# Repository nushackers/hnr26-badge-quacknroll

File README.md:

# hack&Roll 2026 "Quack & Roll" hardware badge

This repository contains both the hardware and firmware source files for the
Hack&Roll 2026 hardware badge.

## License

See the root directory's [LICENSE.md](./LICENSE.md) for more information on how
these materials are licensed.

## Acknowledgements

This Hack&Roll 2026 hardware badge would not have been possible without the
following people:

- **Terence** Chan Zun Mun ([@Hackin7](https://github.com/Hackin7)), for his
  invaluable knowledge and guidance in PCB design and hardware badge
  development, as well as liaising with Espressif Systems
- Lim **Yik Jin** ([@yikjin](https://github.com/yikjin)), for developing the
  hardware badge
- Park **Youngseo** ([@youngseopark05](https://github.com/youngseopark05)), for
  creating the artwork used for this hardware badge
- Koh Chan Hong, **Ravern** ([@ravern](https://github.com/ravern)), for liaising
  with Espressif Systems
- Tan Rongwen, **Daren** ([@darentanrw](https://github.com/darentanrw)), for
  liaising with Espressif Systems
- Everyone in [NUS Hackers](https://www.nushackers.org/) for making Hack&Roll
  2026 a reality!

The ESP32-C3-WROOM-02-N4 module in this hardware badge is also sponsored by
[Espressif Systems](https://www.espressif.com/), the manufacturers of the
widely-used ESP32 chips.

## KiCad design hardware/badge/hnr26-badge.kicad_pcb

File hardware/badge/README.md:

# HnR'26 hardware badge: hardware source files

This directory contains the [KiCad](https://www.kicad.org/) 9 hardware source
files for the Hack&Roll 2026 hardware badge.

## Manufacturing

We used [JLCPCB manufacturing services](https://jlcpcb.com/) for the hardware
badges. To help with component parts assignment and generating JLCPCB-compatible
files, we used the open source
[KiCAD JLCPCB tools](https://github.com/bouni/kicad-jlcpcb-tools) plugin.

## License

The hardware source files in this directory are open-sourced, licensed under
CERN-OHL-P-2.0. See [LICENSE.md](./LICENSE.md) for the full license text.

## Acknowledgements

HnR'26 hardware badge would not have been possible without the following people:

- **Terence** Chan Zun Mun ([@Hackin7](https://github.com/Hackin7)), for his
  invaluable knowledge and guidance in PCB design and hardware badge
  development, as well as liaising with Espressif Systems
- Lim **Yik Jin** ([@yikjin](https://github.com/yikjin)), for developing the
  hardware badge
- Park **Youngseo** ([@youngseopark05](https://github.com/youngseopark05)), for
  creating the artwork used for this hardware badge, and for HnR'26 in general
- **Daren** Tan Rongwen ([@darentanrw](https://github.com/darentanrw)), for
  liaising with Espressif Systems

The ESP32-C3-WROOM-02-N4 module in this hardware badge is also sponsored by
[Espressif Systems](https://www.espressif.com/), the manufacturers of the
widely-used ESP32 chips.

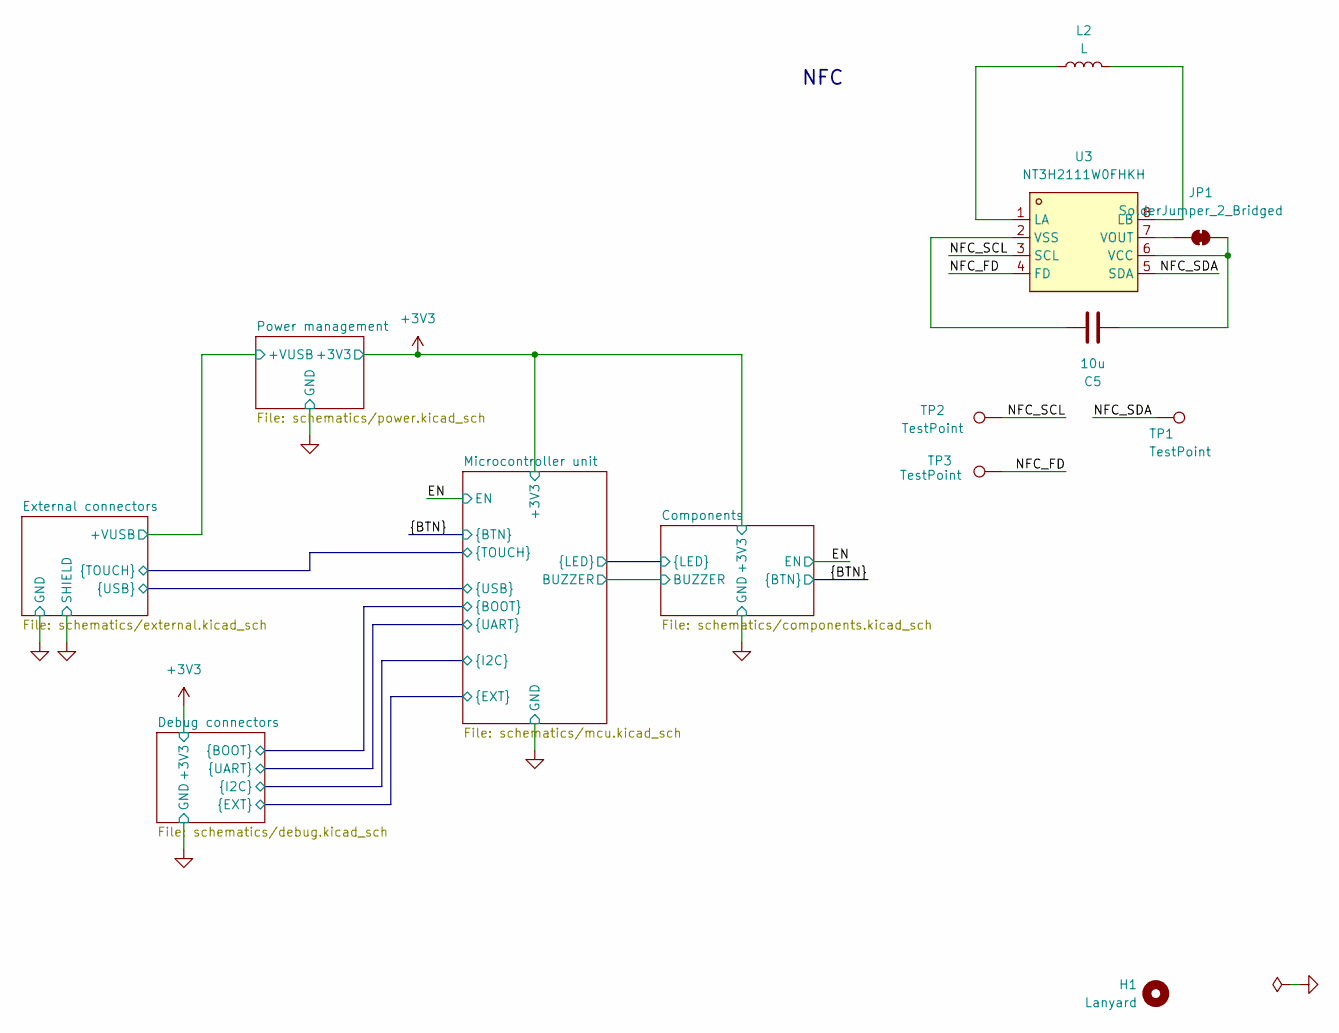
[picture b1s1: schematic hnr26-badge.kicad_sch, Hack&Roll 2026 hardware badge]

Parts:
C5: 10u; C_0805_2012Metric; LCSC Part # C19103847
H1: Lanyard; MountingHole_3.2mm_M3_DIN965_Pad
JP1: SolderJumper_2_Bridged; SolderJumper-2_P1.3mm_Bridged_RoundedPad1.0x1.5mm
L2: L; NFC_COIL
TP1, TP2, TP3: TestPoint; TestPoint_Pad_1.0x1.0mm
U3: NT3H2111W0FHKH; XQFN-8_L1.6-W1.6-P0.50-BL_NT3H2111W0FHKH; LCSC Part C710403

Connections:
/NFC_FD: TP3.1, U3.4 (FD)
/NFC_SCL: TP2.1, U3.3 (SCL)
/NFC_SDA: TP1.1, U3.5 (SDA)
unnamed: C5.2, JP1.1 (A), U3.6 (VCC)
unnamed: JP1.2 (B), U3.7 (VOUT)
unnamed: L2.1, U3.1 (LA)
unnamed: L2.2, U3.8 (LB)
unnamed: C5.1, U3.2 (VSS)

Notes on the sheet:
NFC

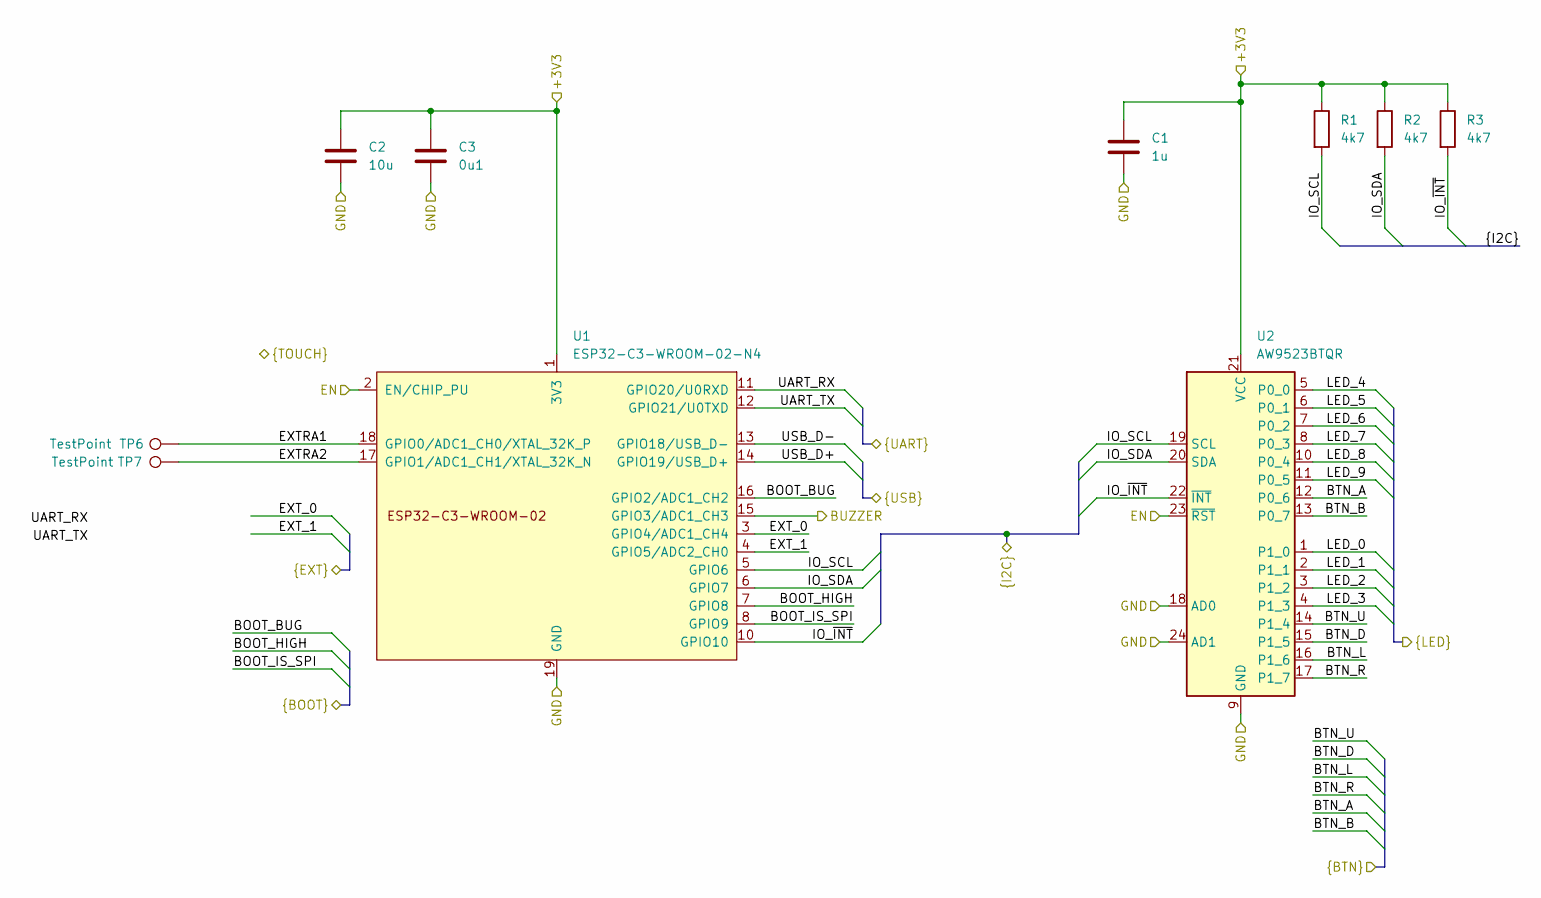
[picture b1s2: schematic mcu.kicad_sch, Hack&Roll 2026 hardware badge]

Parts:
C1: 1u; C_0805_2012Metric; LCSC Part # C344171
C2: 10u; C_0805_2012Metric; LCSC Part # C19103847
C3: 0u1; C_0805_2012Metric; LCSC Part # C5137467
R1, R2, R3: 4k7; R_0805_2012Metric; LCSC Part # C2907326
TP6, TP7: TestPoint; TestPoint_Pad_2.5x2.5mm
U1: ESP32-C3-WROOM-02-N4; ESP32-C3-WROOM-02; LCSC Part # C2934560
U2: AW9523BTQR; QFN-24-1EP_4x4mm_P0.5mm_EP2.7x2.7mm; LCSC Part # C148077

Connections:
+3V3: C1.1, C2.1, C3.1, R1.1, R2.1, R3.1, U1.1 (3V3), U2.21 (VCC); also elsewhere on the board
/BTN_A: U2.12 (P0_6)
/BTN_B: U2.13 (P0_7)
/BTN_D: U2.15 (P1_5); also elsewhere on the board
/BTN_L: U2.16 (P1_6); also elsewhere on the board
/BTN_R: U2.17 (P1_7); also elsewhere on the board
/BTN_U: U2.14 (P1_4); also elsewhere on the board
/Components/BUZZER: U1.15 (GPIO3/ADC1_CH3); also elsewhere on the board
/Components/LED_0: U2.1 (P1_0); also elsewhere on the board
/Components/LED_1: U2.2 (P1_1); also elsewhere on the board
/Components/LED_2: U2.3 (P1_2); also elsewhere on the board
/Components/LED_3: U2.4 (P1_3); also elsewhere on the board
/Components/LED_4: U2.5 (P0_0); also elsewhere on the board
/Components/LED_5: U2.6 (P0_1); also elsewhere on the board
/Components/LED_6: U2.7 (P0_2); also elsewhere on the board
/Components/LED_7: U2.8 (P0_3); also elsewhere on the board
/Components/LED_8: U2.10 (P0_4); also elsewhere on the board
/Components/LED_9: U2.11 (P0_5); also elsewhere on the board
/Debug connectors/BOOT_BUG: U1.16 (GPIO2/ADC1_CH2); also elsewhere on the board
/Debug connectors/BOOT_HIGH: U1.7 (GPIO8); also elsewhere on the board
/Debug connectors/BOOT_IS_SPI: U1.8 (GPIO9); also elsewhere on the board
/Debug connectors/EXT_0: U1.3 (GPIO4/ADC1_CH4); also elsewhere on the board
/Debug connectors/EXT_1: U1.4 (GPIO5/ADC2_CH0); also elsewhere on the board
/Debug connectors/UART_RX: U1.11 (GPIO20/U0RXD); also elsewhere on the board
/Debug connectors/UART_TX: U1.12 (GPIO21/U0TXD); also elsewhere on the board
/EN: U1.2 (EN/CHIP_PU), U2.23 (~RST); also elsewhere on the board
/External connectors/USB_D+: U1.14 (GPIO19/USB_D+); also elsewhere on the board
/External connectors/USB_D-: U1.13 (GPIO18/USB_D-); also elsewhere on the board
/Microcontroller unit/EXTRA1: TP6.1, U1.18 (GPIO0/ADC1_CH0/XTAL_32K_P)
/Microcontroller unit/EXTRA2: TP7.1, U1.17 (GPIO1/ADC1_CH1/XTAL_32K_N)
/Microcontroller unit/IO_SCL: R1.2, U1.5 (GPIO6), U2.19 (SCL); also elsewhere on the board
/Microcontroller unit/IO_SDA: R2.2, U1.6 (GPIO7), U2.20 (SDA); also elsewhere on the board
/Microcontroller unit/IO_~INT: R3.2, U1.10 (GPIO10), U2.22 (~INT)
GND: C1.2, C2.2, C3.2, U1.9 (GND), U1.19 (GND), U2.9 (GND), U2.18 (AD0), U2.24 (AD1), U2.25 (GND); also elsewhere on the board

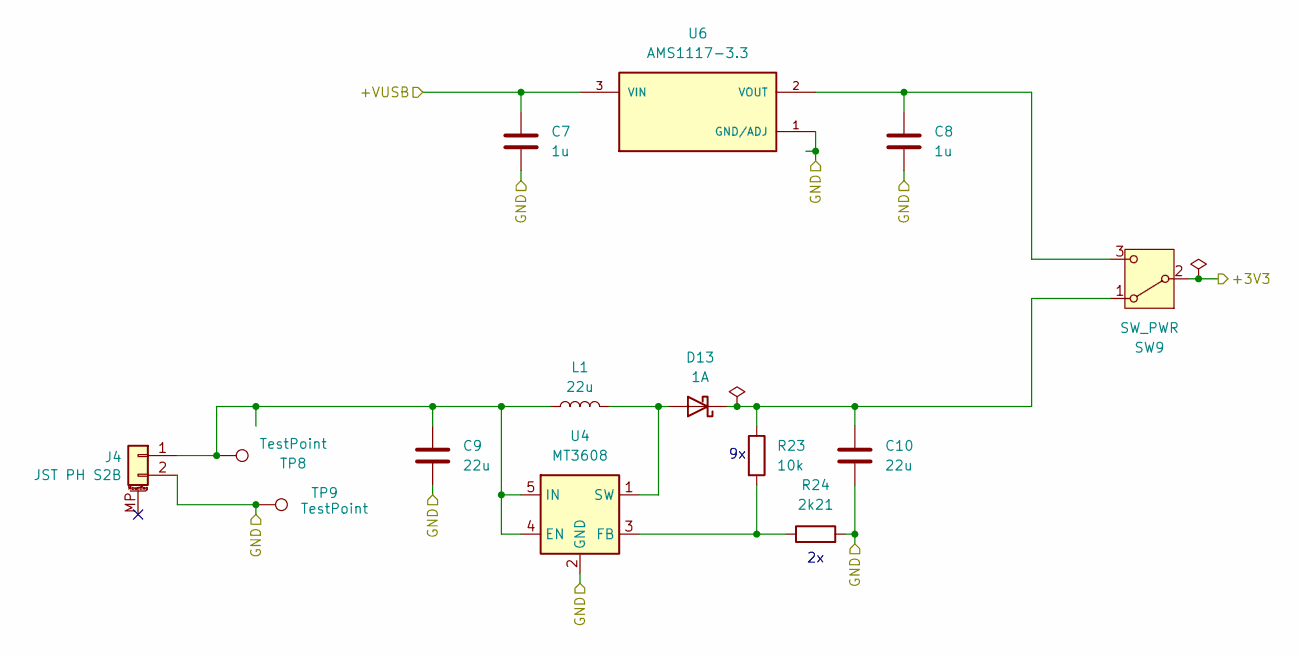
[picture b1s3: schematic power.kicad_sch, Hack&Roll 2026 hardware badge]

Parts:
C7, C8: 1u; C_0805_2012Metric; LCSC Part # C344171
C9, C10: 22u; C_0805_2012Metric; LCSC Part # C5674
D13: 1A; D_0805_2012Metric; LCSC Part # C143773
J4: JST PH S2B; JST_PH_S2B-PH-SM4-TB_1x02-1MP_P2.00mm_Horizontal; LCSC C505023
L1: 22u; L_0805_2012Metric; LCSC Part # C32375
R23: 10k; R_0805_2012Metric; LCSC Part # C2930231
R24: 2k21; R_0805_2012Metric; LCSC Part # C5121533
SW9: SW_PWR; SW-SMD_SK-01A-H1.5; LCSC Part # C778186
TP8, TP9: TestPoint; TestPoint_Pad_4.0x4.0mm
U4: MT3608; SOT-23-6; LCSC Part # C84817
U6: AMS1117-3.3; SOT-89-3_L4.5-W2.5-P1.50-LS4.2-BR; PARTREV N/A

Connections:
+3V3: SW9.2 (B); also elsewhere on the board
/External connectors/+VUSB: C7.1, U6.3 (VIN); also elsewhere on the board
GND: C7.2, C8.2, C9.2, C10.2, J4.2, R24.2, TP9.1, U4.2 (GND), U6.1 (GND/ADJ); also elsewhere on the board
unnamed: D13.2 (A), L1.2, U4.1 (SW)
unnamed: C10.1, D13.1 (K), R23.1, SW9.1 (A)
unnamed: C9.1, J4.1, L1.1, TP8.1, U4.4 (EN), U4.5 (IN)
unnamed: C8.1, SW9.3 (C), U6.2 (VOUT)
unnamed: R23.2, R24.1, U4.3 (FB)

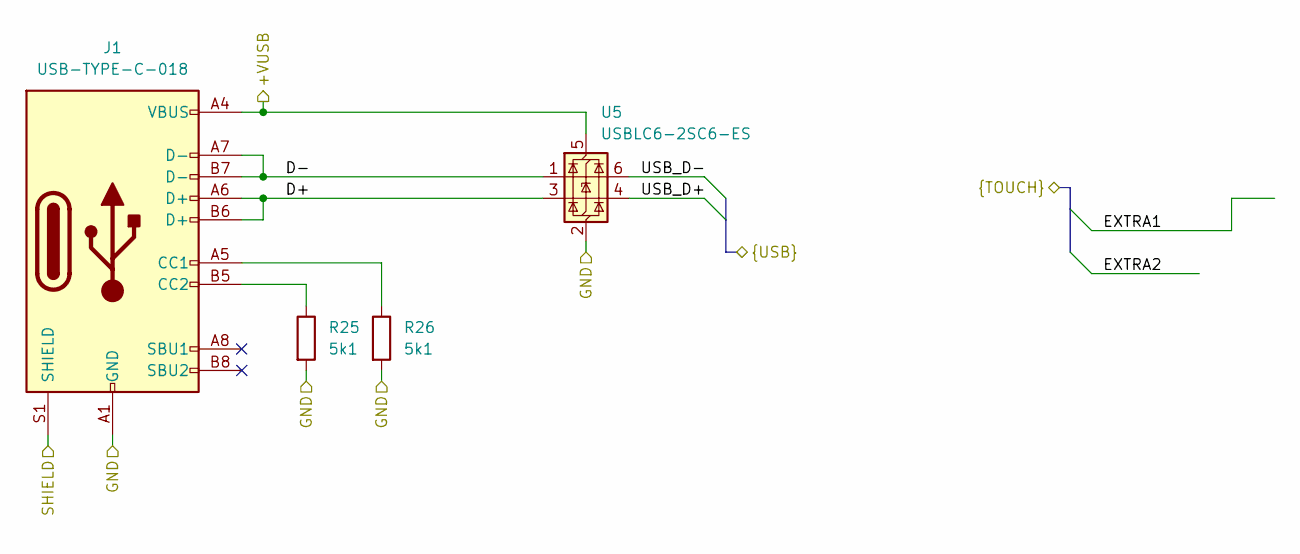
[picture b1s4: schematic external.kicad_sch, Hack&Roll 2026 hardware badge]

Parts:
J1: USB-TYPE-C-018; USB_C_Receptacle_GCT_USB4105-xx-A_16P_TopMnt_Horizontal; LCSC Part # C2927038
R25, R26: 5k1; R_0805_2012Metric; LCSC Part # C22356678
U5: USBLC6-2SC6-ES; SOT-23-6; LCSC Part # C5180249

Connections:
/External connectors/+VUSB: J1.A4 (VBUS), J1.A9 (VBUS), J1.B4 (VBUS), J1.B9 (VBUS), U5.5 (VBUS); also elsewhere on the board
/External connectors/D+: J1.A6 (D+), J1.B6 (D+), U5.3 (I/O2)
/External connectors/D-: J1.A7 (D-), J1.B7 (D-), U5.1 (I/O1)
/External connectors/USB_D+: U5.4 (I/O2); also elsewhere on the board
/External connectors/USB_D-: U5.6 (I/O1); also elsewhere on the board
GND: J1.A1 (GND), J1.A12 (GND), J1.B1 (GND), J1.B12 (GND), J1.S1 (SHIELD), R25.2, R26.2, U5.2 (GND); also elsewhere on the board
unnamed: J1.A5 (CC1), R26.1
unnamed: J1.B5 (CC2), R25.1

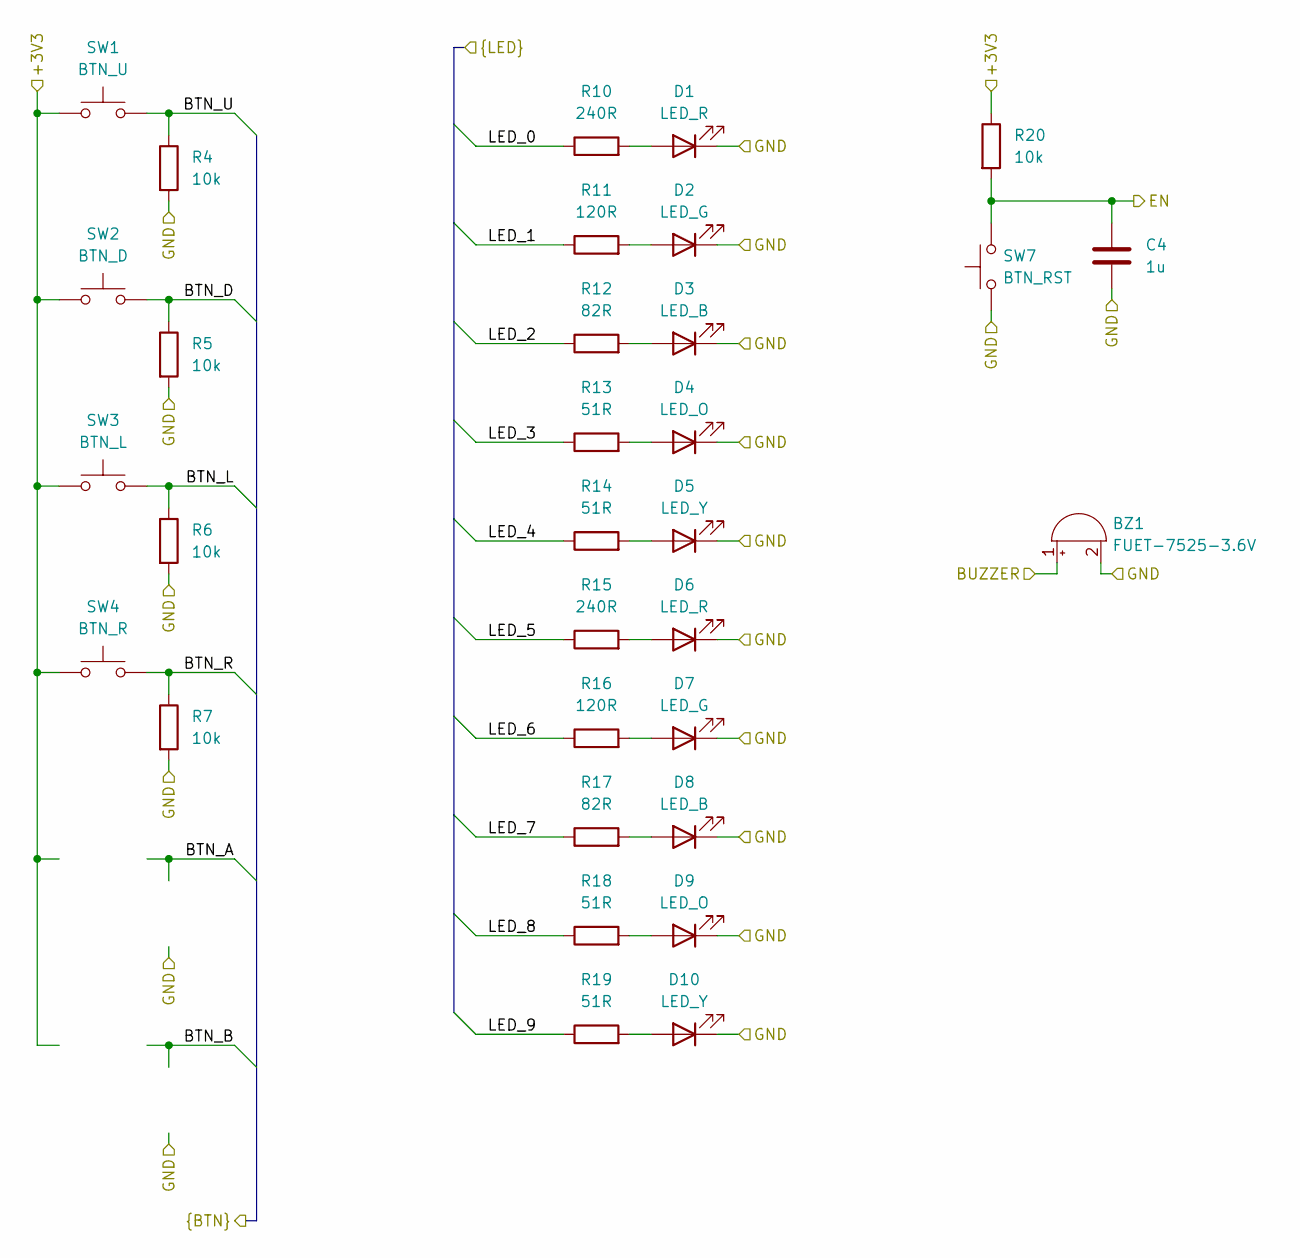
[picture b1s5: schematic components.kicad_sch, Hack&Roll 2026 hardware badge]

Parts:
BZ1: FUET-7525-3.6V; Buzzer-SMD_4P-L7.5-W7.5-BR; LCSC Part # C417427
C4: 1u; C_0805_2012Metric; LCSC Part # C344171
D1, D6: LED_R; LED_0805_2012Metric; LCSC Part # C7496834
D2, D7: LED_G; LED_0805_2012Metric; LCSC Part # C7496832
D3, D8: LED_B; LED_0805_2012Metric; LCSC Part # C7496833
D4, D9: LED_O; LED_0805_2012Metric; LCSC Part # C965813
D5, D10: LED_Y; LED_0805_2012Metric; LCSC Part # C965814
R4, R5, R6, R7, R20: 10k; R_0805_2012Metric; LCSC Part # C2930231
R10, R15: 240R; R_0805_2012Metric; LCSC Part # C25296
R11, R16: 120R; R_0805_2012Metric; LCSC Part # C3013232
R12, R17: 82R; R_0805_2012Metric; LCSC Part # C2907344
R13, R14, R18, R19: 51R; R_0805_2012Metric; LCSC Part # C2907334
SW1: BTN_U; SW_Push_1P1T_XKB_TS-1187A; LCSC Part # C2888877
SW2: BTN_D; SW_Push_1P1T_XKB_TS-1187A; LCSC Part # C2888877
SW3: BTN_L; SW_Push_1P1T_XKB_TS-1187A; LCSC Part # C2888877
SW4: BTN_R; SW_Push_1P1T_XKB_TS-1187A; LCSC Part # C2888877
SW7: BTN_RST; SW_Push_1P1T_XKB_TS-1187A; LCSC Part # C2888877

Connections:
+3V3: R20.1, SW1.1, SW2.1, SW3.1, SW4.1; also elsewhere on the board
/BTN_D: R5.1, SW2.2; also elsewhere on the board
/BTN_L: R6.1, SW3.2; also elsewhere on the board
/BTN_R: R7.1, SW4.2; also elsewhere on the board
/BTN_U: R4.1, SW1.2; also elsewhere on the board
/Components/BUZZER: BZ1.1 (+); also elsewhere on the board
/Components/LED_0: R10.1; also elsewhere on the board
/Components/LED_1: R11.1; also elsewhere on the board
/Components/LED_2: R12.1; also elsewhere on the board
/Components/LED_3: R13.1; also elsewhere on the board
/Components/LED_4: R14.1; also elsewhere on the board
/Components/LED_5: R15.1; also elsewhere on the board
/Components/LED_6: R16.1; also elsewhere on the board
/Components/LED_7: R17.1; also elsewhere on the board
/Components/LED_8: R18.1; also elsewhere on the board
/Components/LED_9: R19.1; also elsewhere on the board
/EN: C4.1, R20.2, SW7.2; also elsewhere on the board
GND: BZ1.2 (-), C4.2, D1.1 (K), D2.1 (K), D3.1 (K), D4.1 (K), D5.1 (K), D6.1 (K), D7.1 (K), D8.1 (K), D9.1 (K), D10.1 (K), R4.2, R5.2, R6.2, R7.2, SW7.1; also elsewhere on the board
unnamed: D1.2 (A), R10.2
unnamed: D2.2 (A), R11.2
unnamed: D3.2 (A), R12.2
unnamed: D4.2 (A), R13.2
unnamed: D5.2 (A), R14.2
unnamed: D6.2 (A), R15.2
unnamed: D7.2 (A), R16.2
unnamed: D8.2 (A), R17.2
unnamed: D9.2 (A), R18.2
unnamed: D10.2 (A), R19.2

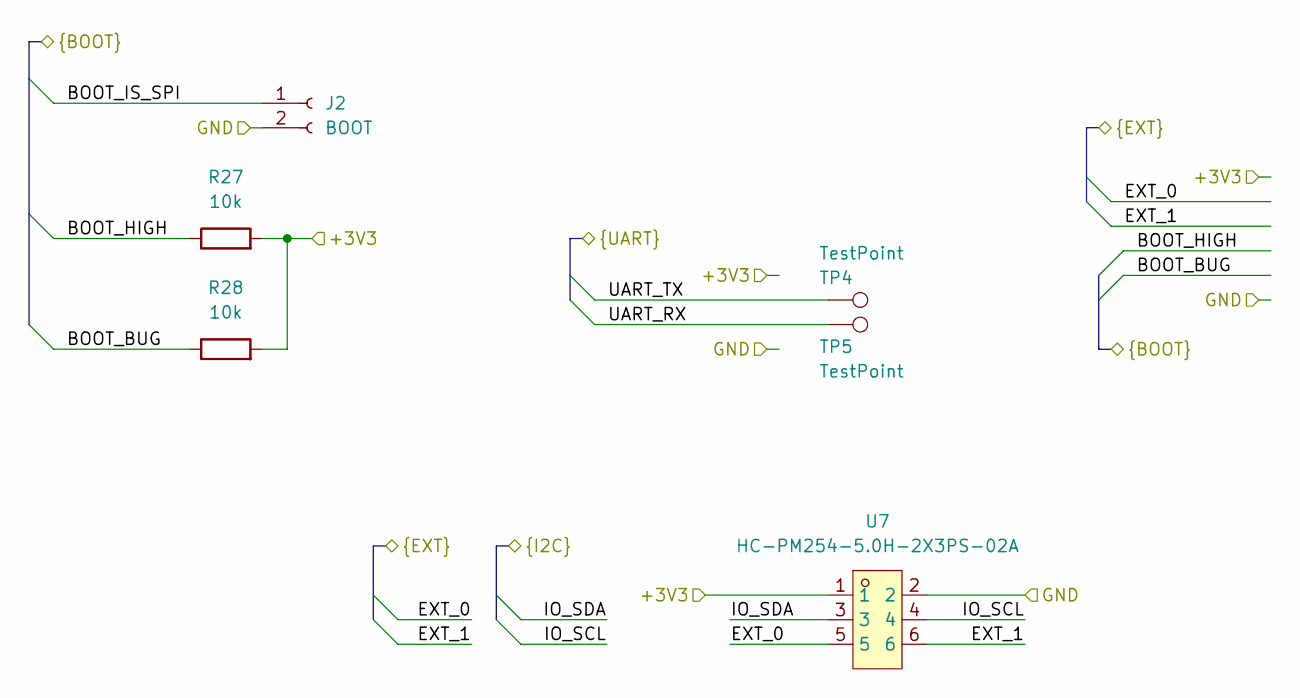
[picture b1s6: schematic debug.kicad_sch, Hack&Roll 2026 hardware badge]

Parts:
J2: BOOT; PinSocket_1x02_P2.54mm_Vertical
R27, R28: 10k; R_0805_2012Metric; LCSC Part # C2930231
TP4, TP5: TestPoint; TestPoint_Pad_2.5x2.5mm
U7: HC-PM254-5.0H-2X3PS-02A; CONN-SMD_HC-PM254-5.0H-2X3PS-02A; LCSC Part C42163131

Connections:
+3V3: R27.2, R28.2, U7.1; also elsewhere on the board
/Debug connectors/BOOT_BUG: R28.1; also elsewhere on the board
/Debug connectors/BOOT_HIGH: R27.1; also elsewhere on the board
/Debug connectors/BOOT_IS_SPI: J2.1; also elsewhere on the board
/Debug connectors/EXT_0: U7.5; also elsewhere on the board
/Debug connectors/EXT_1: U7.6; also elsewhere on the board
/Debug connectors/UART_RX: TP5.1; also elsewhere on the board
/Debug connectors/UART_TX: TP4.1; also elsewhere on the board
/Microcontroller unit/IO_SCL: U7.4; also elsewhere on the board
/Microcontroller unit/IO_SDA: U7.3; also elsewhere on the board
GND: J2.2, U7.2; also elsewhere on the board

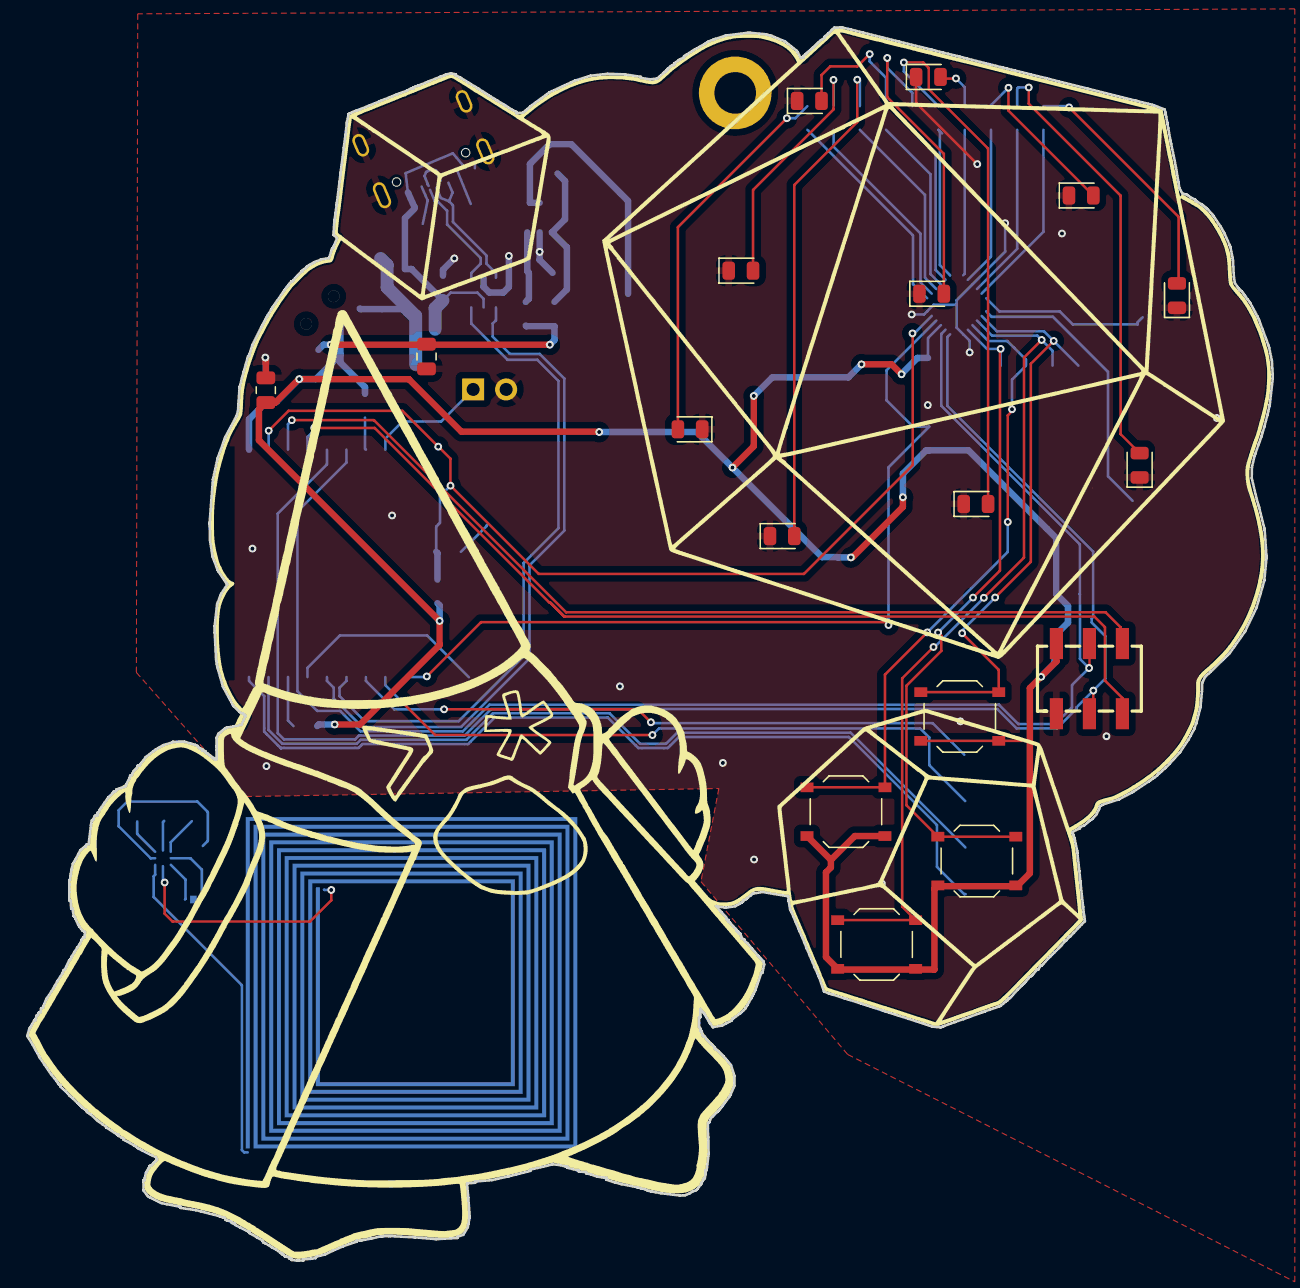
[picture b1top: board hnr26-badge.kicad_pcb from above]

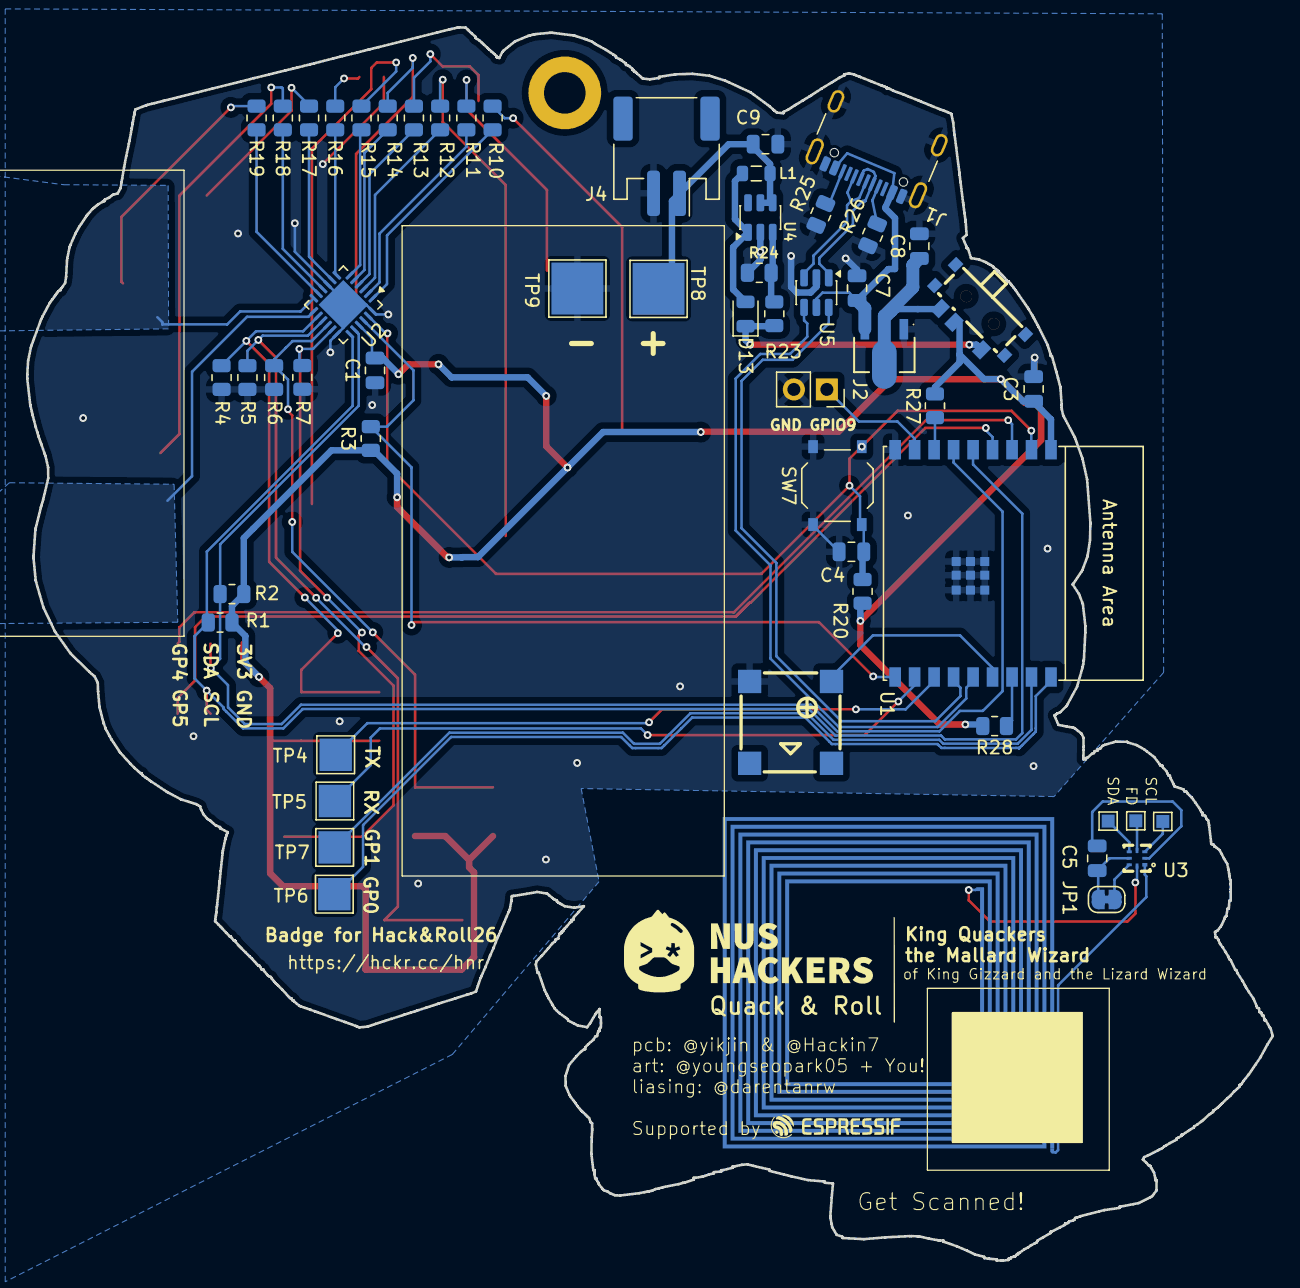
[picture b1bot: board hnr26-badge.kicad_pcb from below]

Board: 2 copper layers, 95.9 x 95.0 mm, 74 parts (56 on the bottom side), 60 nets.

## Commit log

2026-01-17 chore: init
